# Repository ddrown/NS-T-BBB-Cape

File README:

original cape design taken from Casey Kuhns/Sparkfun - https://github.com/sparkfun/BeagleBone_Black_Proto_Cape

Parts:

U$2 - PI6C4511WE-ND - 8-SOIC PLL - $2.17
U$3 - Navspark NS-T - GPS Receiver - $80
U$4 - 24LC32A-I/SN-ND - 8SOIC I2C 32KBIT EEPROM - $0.41
Cape connectors - 3x S1012EC-40-ND - 0.1" MALE 40POS - $0.56/ea
Navspark socket - 
	1x S7011-ND - 0.1" 13POS FEMALE - $1.06
	1x S6100-ND - 0.1" 12POS FEMALE - $0.98
R1 - 1x 1276-5241-1-ND - RES SMD 270 OHM 1% 1/8W 0805 - $0.10
C2 - 1x 490-1664-1-ND - CAP CER 10000PF 50V 10% X7R 0805 - $0.10

Datasheets:

U$2/PLL - http://www.pericom.com/assets/Datasheets/PI6C4511.pdf
U$3/GPS - http://navspark.mybigcommerce.com/ns-t-precision-timing-mode-gps-receiver/
U$4/EEPROM - http://ww1.microchip.com/downloads/en/DeviceDoc/21713M.pdf

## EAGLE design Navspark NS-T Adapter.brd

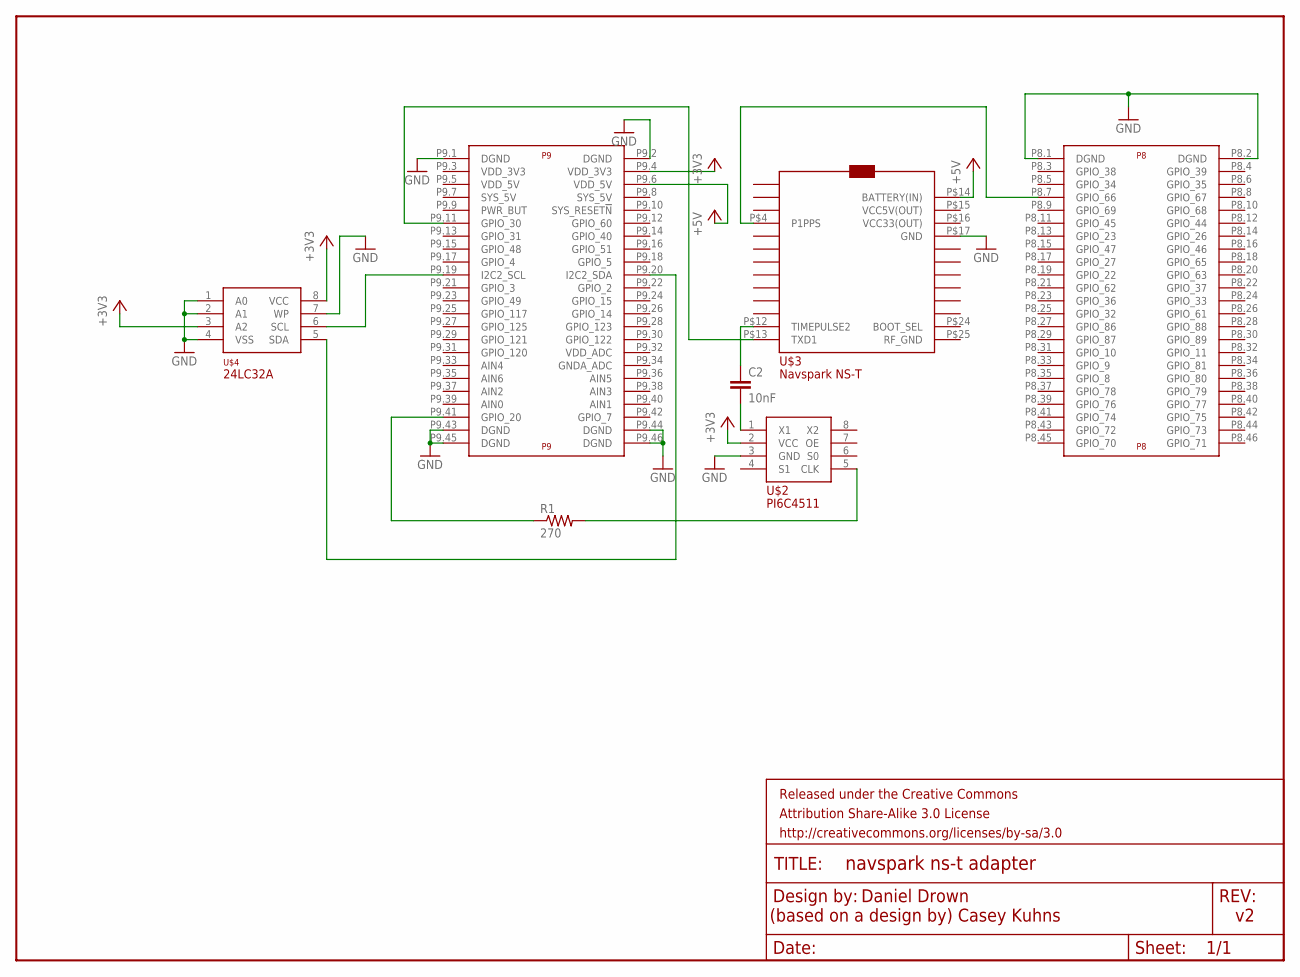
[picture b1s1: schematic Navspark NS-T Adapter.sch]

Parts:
C2: 10nF; 0805
FRAME1: FRAME-LETTER; CREATIVE_COMMONS
R1: 270; 0805
U$1: BEAGLE_BONE_BLACK_CAPE
U$2: PI6C4511WE; 8-SOIC
U$3: NS-T; BREADBOARD
U$4: 24LC32A; SOIC8

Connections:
+5V: U$1.P9.6 (VDD_5V), U$3.P$14 (BATTERY(IN))
GND: U$1.P8.1 (DGND), U$1.P8.2 (DGND), U$1.P9.1 (DGND), U$1.P9.2 (DGND), U$1.P9.43 (DGND), U$1.P9.44 (DGND), U$1.P9.45 (DGND), U$1.P9.46 (DGND), U$2.3 (GND), U$3.P$17 (GND), U$4.1 (A0), U$4.2 (A1), U$4.4 (VSS), U$4.7 (WP)
unnamed: U$1.P9.19 (I2C2_SCL), U$4.6 (SCL)
unnamed: U$1.P8.7 (GPIO_66), U$3.P$4 (P1PPS)
unnamed: U$1.P9.11 (GPIO_30), U$3.P$13 (TXD1)
unnamed: R1.1, U$1.P9.41 (GPIO_20)
unnamed: C2.1, U$3.P$12 (TIMEPULSE2)
unnamed: U$1.P9.20 (I2C2_SDA), U$4.5 (SDA)
unnamed: U$1.P9.4 (VDD_3V3), U$2.2 (VCC), U$4.3 (A2), U$4.8 (VCC)
unnamed: C2.2, U$2.1 (X1)
unnamed: R1.2, U$2.5 (CLK)

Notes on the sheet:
Daniel Drown (based on a design by) Casey Kuhns

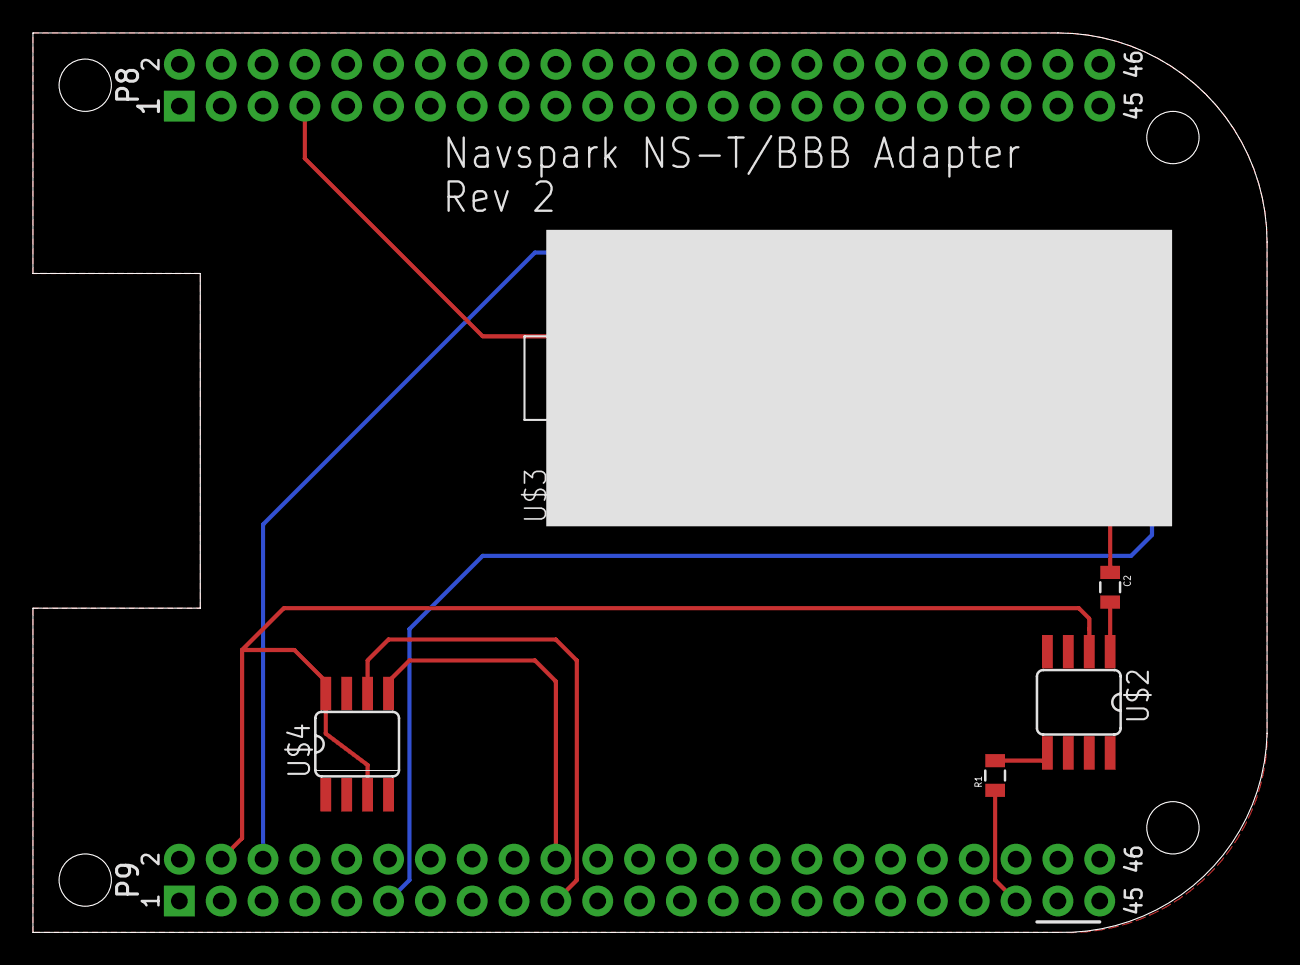
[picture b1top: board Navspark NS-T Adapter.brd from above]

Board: 2 copper layers, 74.9 x 54.6 mm, 7 parts (0 on the bottom side), 11 nets.

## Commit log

2015-03-21 Revision 1
2015-03-22 remove PLL OE -> GND, rely on internal pullup
2015-04-11 revision 2: decouple NS-T/PI6C4511, add limiting resistor between PI6C4511 and BBB

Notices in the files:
parts and their libraries:
SparkFun-Boards: Licensing: CC v3.0 Share-Alike You are welcome to use this library for commercial purposes.
SparkFun-Aesthetics: Released under the Creative Commons Attribution Share-Alike 3.0 License
SparkFun-Aesthetics: http://creativecommons.org/licenses/by-sa/3.0
